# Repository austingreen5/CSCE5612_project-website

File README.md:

# CSCE5612_project-website
CSCE 5612 Project Website Link - https://austingreen5.github.io/CSCE5612_project-website/

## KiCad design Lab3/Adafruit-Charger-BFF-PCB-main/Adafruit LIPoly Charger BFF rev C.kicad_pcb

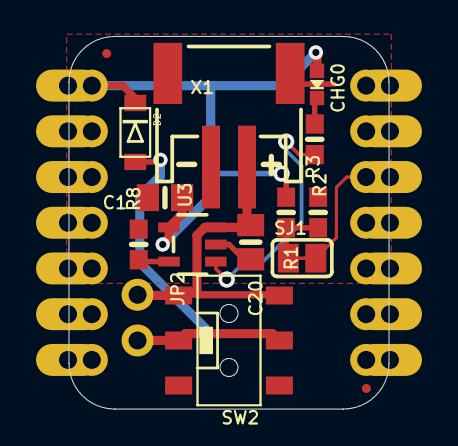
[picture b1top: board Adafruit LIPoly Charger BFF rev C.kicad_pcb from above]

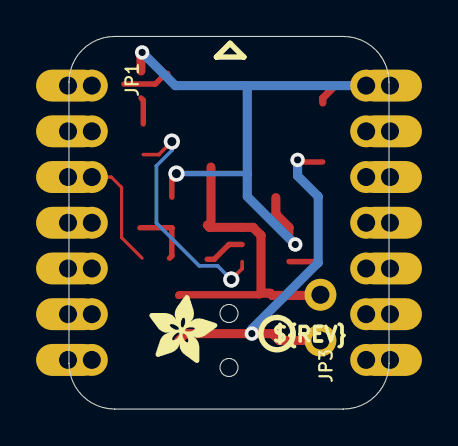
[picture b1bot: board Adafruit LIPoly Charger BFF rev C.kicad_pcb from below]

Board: 16 copper layers, 17.8 x 20.7 mm, 34 parts (7 on the bottom side), 9 nets.

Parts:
C1, C20: 10uF; 0805-NO
CHG0: ORANGE; CHIPLED_0603_NOOUTLINE
D2: MBR120; SOD-123FL
JP1, JP3: 1X07_CASTEL
JP2: 1X02_ROUND
PLABEL0: PLABEL0
PLABEL1: PLABEL1
PLABEL2: PLABEL2
PLABEL3: PLABEL3
PLABEL4: PLABEL4
PLABEL5: PLABEL5
PLABEL6: PLABEL6
PLABEL7: PLABEL7
PLABEL8: PLABEL8
PLABEL9: PLABEL9
PLABEL10: PLABEL10
PLABEL11: PLABEL11
PLABEL12: PLABEL12
PLABEL13: PLABEL13
PLABEL14: PLABEL14
R1, R3: 100K; 0603-NO
R2, R8: 5.1K; 0603-NO
SJ1: SOLDERJUMPER_CLOSEDWIRE
SW2: EG1390
U3: MCP73831T-2ACI/OT; SOT23-5
U$2: ADAFRUIT_3.5MM
U$3: PCBFEAT-REV-040
U$6, U$8: FIDUCIAL_0.5MM
X1: JSTPH; JSTPH2_BATT

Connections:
+5V: C1.1, CHG0.A, D2.C, JP3.7, JP3.7C, R1.1, U3.4
A2: JP1.3, JP1.3C, SJ1.2
GND: C1.2, C20.2, JP3.6, JP3.6C, R3.2, R8.2, U3.2, X1.1, X1.NC1, X1.NC2
unnamed: R1.2, R3.1, SJ1.1
unnamed: CHG0.C, R2.1
unnamed: R2.2, U3.1
unnamed: R8.1, U3.5
unnamed: D2.A, JP2.2, SW2.P1, SW2.P2
VBAT: C20.1, JP2.1, SW2.S1, SW2.S2, U3.3, X1.2

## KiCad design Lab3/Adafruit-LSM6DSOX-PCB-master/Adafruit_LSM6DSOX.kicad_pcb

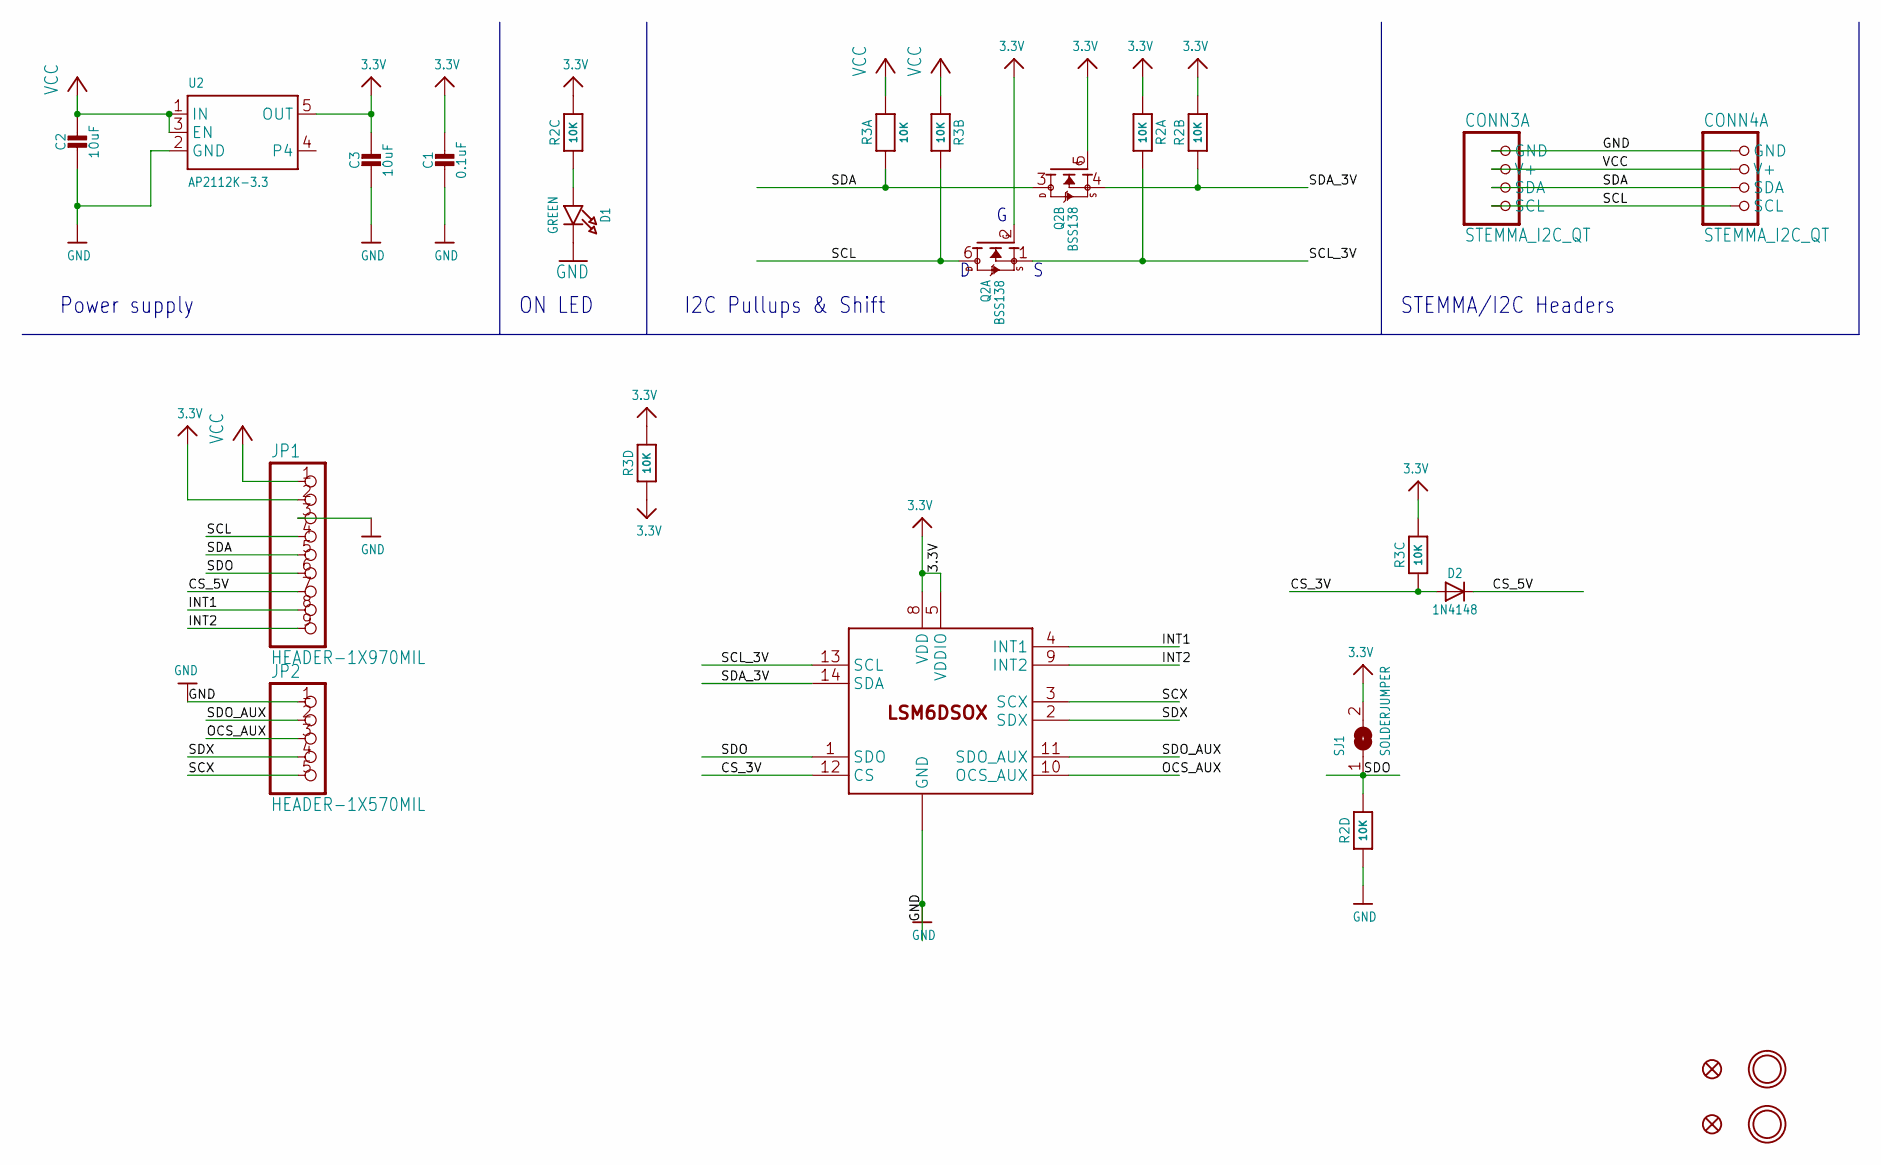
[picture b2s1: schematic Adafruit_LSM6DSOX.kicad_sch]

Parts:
C1: 0.1uF; 0603-NO
C2, C3: 10uF; 0805-NO
CONN3, CONN4: STEMMA_I2C_QT; JST_SH4
D1: GREEN; CHIPLED_0603_NOOUTLINE
D2: 1N4148; SOD-323
FID3, FID4: FIDUCIAL_1MM
JP1: HEADER-1X970MIL; 1X09_ROUND_70
JP2: HEADER-1X570MIL; 1X05_ROUND_70
Q2: BSS138; SOT363
R2, R3: 10K; RESPACK_4X0603
SJ1: SOLDERJUMPER; SOLDERJUMPER_ARROW_NOPASTE
U2: AP2112K-3.3; SOT23-5
U$1, U$17: MOUNTINGHOLE2.5; MOUNTINGHOLE_2.5_PLATED
U$2: LSM6DSOX; LGA-14L

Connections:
3.3V: C1.1, C3.1, JP1.2, Q2.2 (G), Q2.5 (G), R2.1, R2.2 (1), R2.6 (2), R3.3 (1), R3.4 (1), R3.5 (2), SJ1.2, U2.5 (OUT), U$2.5 (VDDIO), U$2.8 (VDD)
CS_3V: D2.A, R3.6 (2), U$2.12 (CS)
CS_5V: D2.C, JP1.7
GND: C1.2, C2.2, C3.2, CONN3.1 (GND), CONN4.1 (GND), D1.C, JP1.3, JP2.1, R2.4 (1), U2.2 (GND), U$2.6 (GND), U$2.7 (GND)
INT1: JP1.8, U$2.4 (INT1)
INT2: JP1.9, U$2.9 (INT2)
unnamed: D1.A, R2.3 (1)
OCS_AUX: JP2.3, U$2.10 (OCS_AUX)
SCL: CONN3.4 (SCL), CONN4.4 (SCL), JP1.4, Q2.6 (D), R3.2 (1)
SCL_3V: Q2.1 (S), R2.8 (2), U$2.13 (SCL)
SCX: JP2.5, U$2.3 (SCX)
SDA: CONN3.3 (SDA), CONN4.3 (SDA), JP1.5, Q2.3 (D), R3.1
SDA_3V: Q2.4 (S), R2.7 (2), U$2.14 (SDA)
SDO: JP1.6, R2.5 (2), SJ1.1, U$2.1 (SDO)
SDO_AUX: JP2.2, U$2.11 (SDO_AUX)
SDX: JP2.4, U$2.2 (SDX)
VCC: C2.1, CONN3.2 (V+), CONN4.2 (V+), JP1.1, R3.7 (2), R3.8 (2), U2.1 (IN), U2.3 (EN)

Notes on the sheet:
ON LED
I2C Pullups & Shift
STEMMA/I2C Headers
Power supply

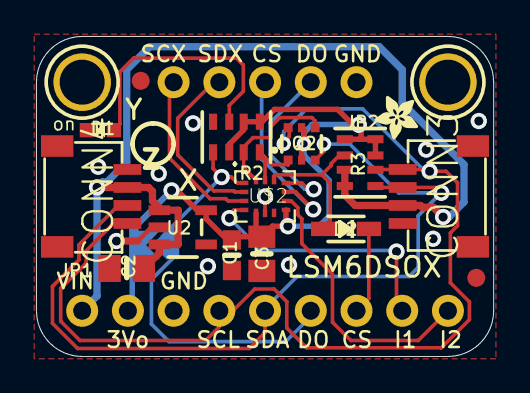
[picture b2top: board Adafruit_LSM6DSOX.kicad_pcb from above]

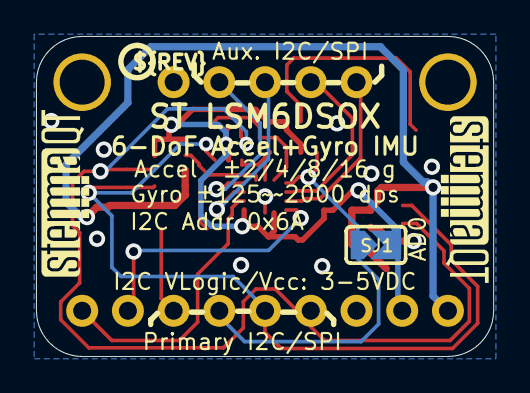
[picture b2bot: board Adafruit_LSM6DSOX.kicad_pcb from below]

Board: 2 copper layers, 25.4 x 17.8 mm, 23 parts (4 on the bottom side), 17 nets.

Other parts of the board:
U$9: ADAFRUIT_2.5MM
U$25: PCBFEAT-REV-040
U$30, U$31: STEMMAQT

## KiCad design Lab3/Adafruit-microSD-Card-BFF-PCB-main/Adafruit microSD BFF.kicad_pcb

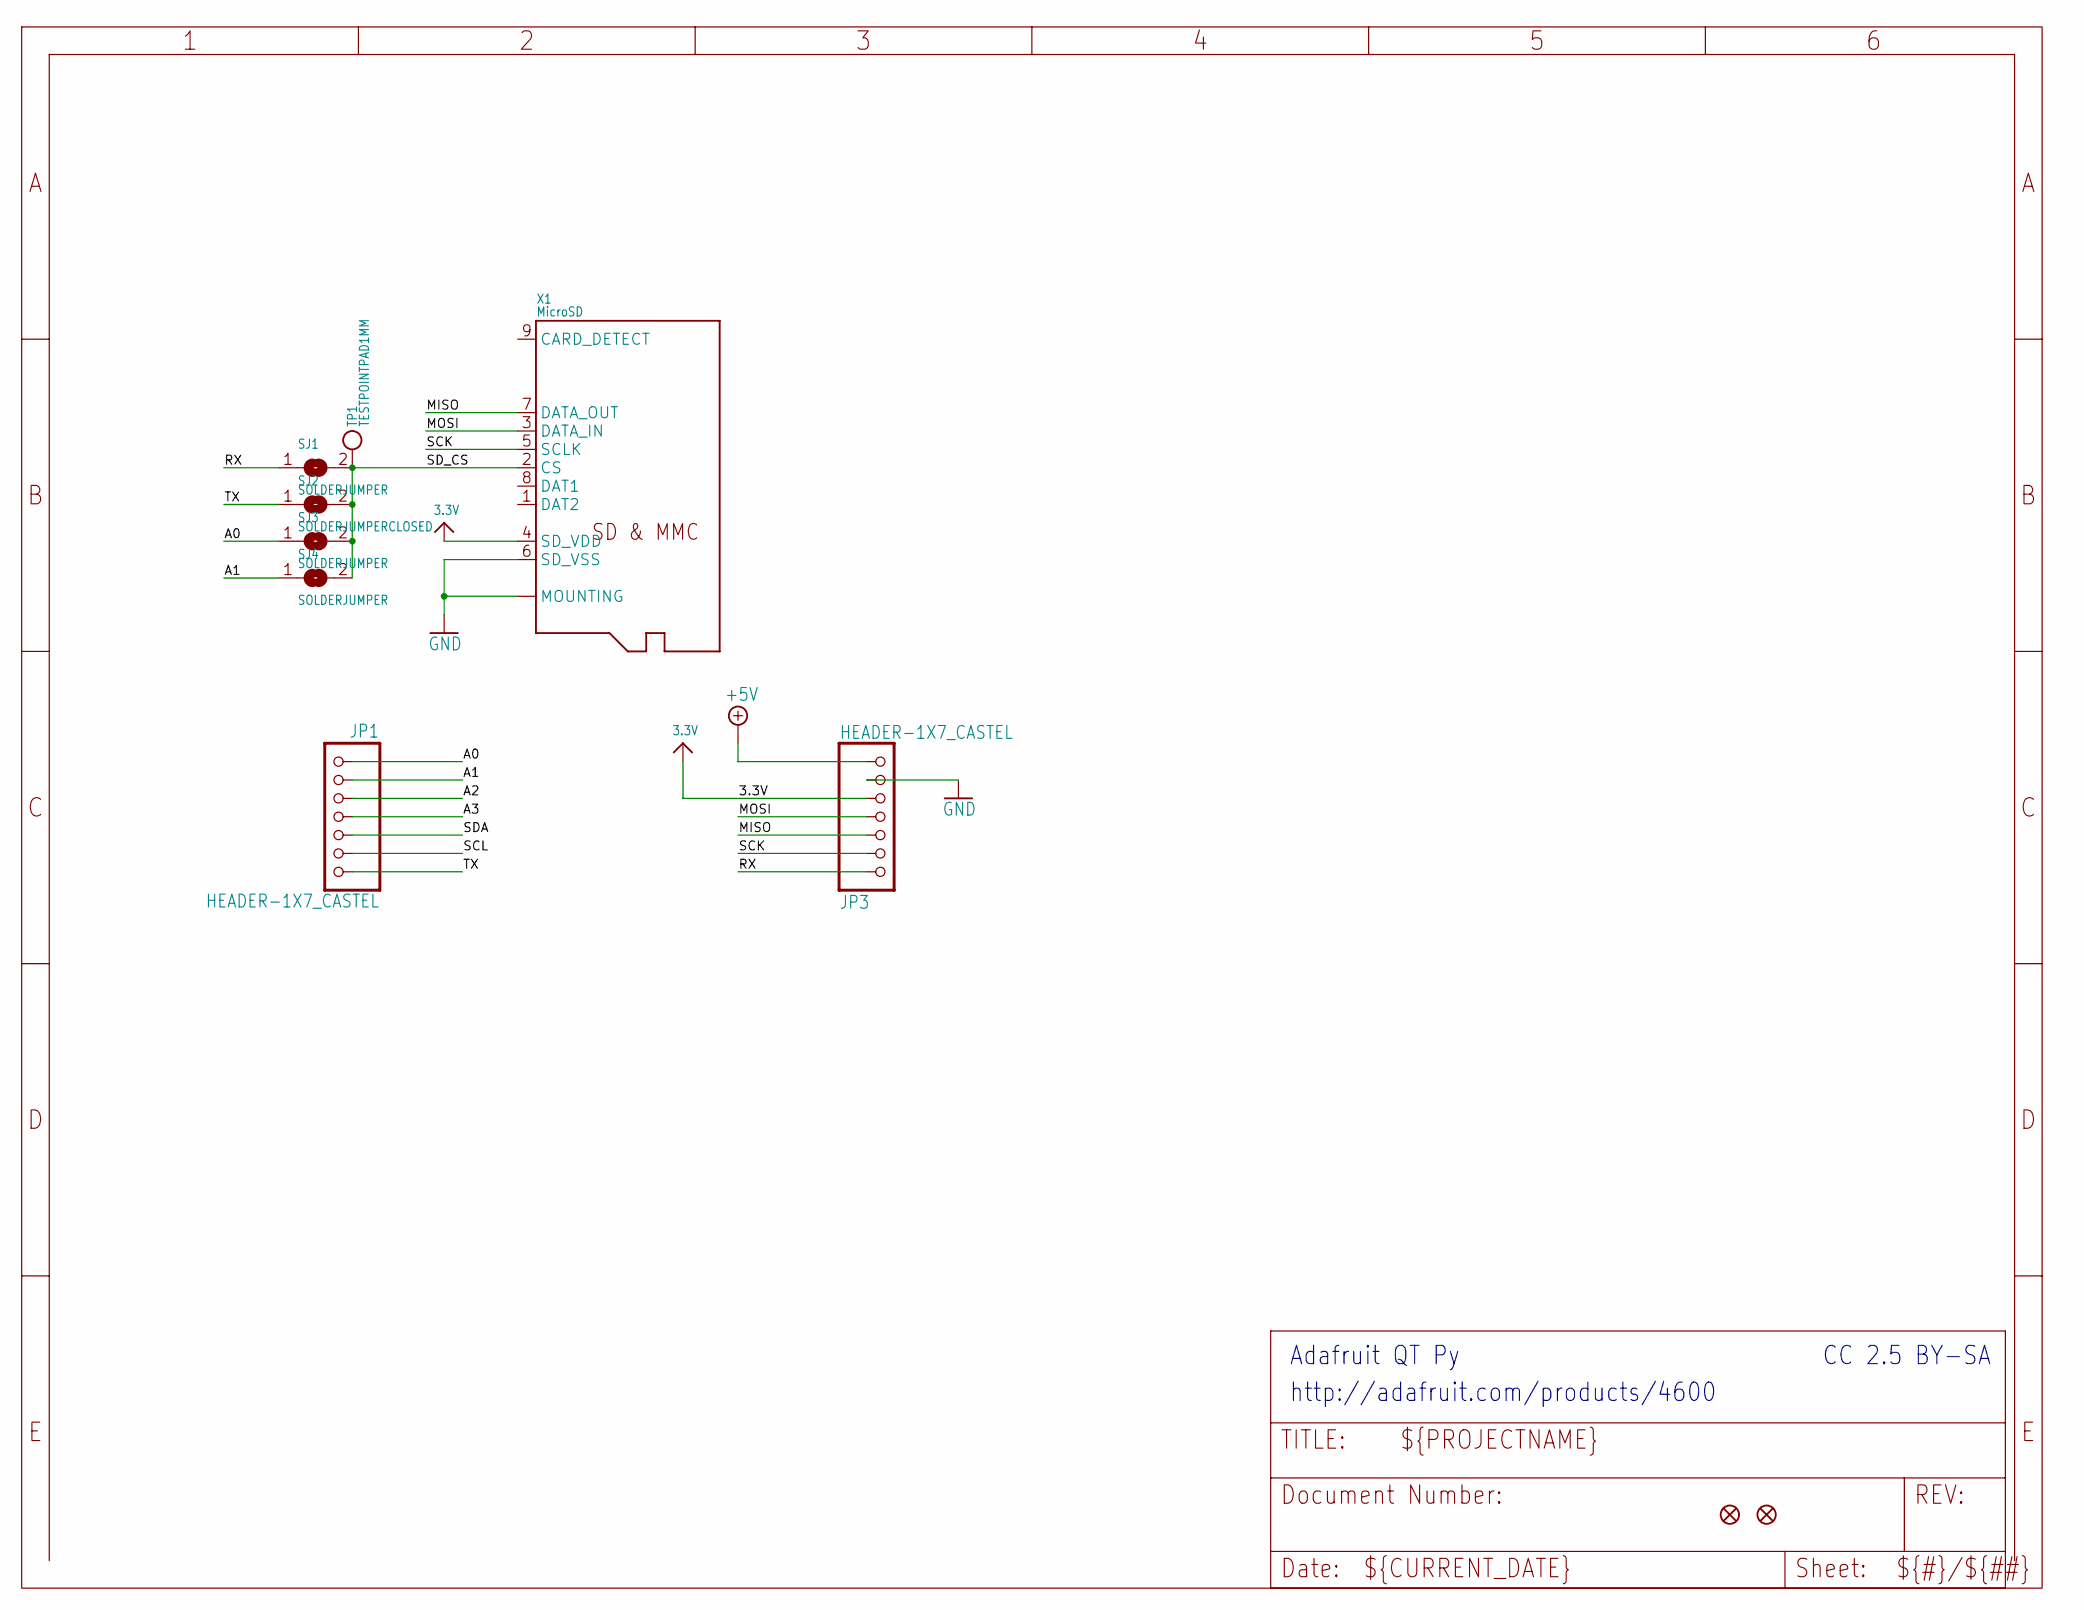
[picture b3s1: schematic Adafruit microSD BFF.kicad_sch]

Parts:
JP1, JP3: HEADER-1X7_CASTEL; 1X07_CASTEL
SJ1, SJ3, SJ4: SOLDERJUMPER; SOLDERJUMPER_ARROW_NOPASTE
SJ2: SOLDERJUMPERCLOSED; SOLDERJUMPER_CLOSEDWIRE
TP1: TESTPOINTPAD1MM; TESTPOINT_PAD_1MM
U$6, U$8: FIDUCIAL_1MM
X1: MicroSD; MOLEX_104031-0811

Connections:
3.3V: JP3.5, JP3.5C (5), X1.4 (SD_VDD)
+5V: JP3.7, JP3.7C (7)
A0: JP1.1, JP1.1C (1), SJ3.1
A1: JP1.2, JP1.2C (2), SJ4.1
A2: JP1.3, JP1.3C (3)
A3: JP1.4, JP1.4C (4)
GND: JP3.6, JP3.6C (6), X1.6 (SD_VSS), X1.10 (MOUNTING), X1.G1 (MOUNTING), X1.G2 (MOUNTING), X1.G3 (MOUNTING), X1.G4 (MOUNTING)
MISO: JP3.3, JP3.3C (3), X1.7 (DATA_OUT)
MOSI: JP3.4, JP3.4C (4), X1.3 (DATA_IN)
RX: JP3.1, JP3.1C (1), SJ1.1
SCK: JP3.2, JP3.2C (2), X1.5 (SCLK)
SCL: JP1.6, JP1.6C (6)
SDA: JP1.5, JP1.5C (5)
SD_CS: SJ1.2, SJ2.2, SJ3.2, SJ4.2, TP1.P$1, X1.2 (CS)
TX: JP1.7, JP1.7C (7), SJ2.1

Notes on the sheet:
http://adafruit.com/products/4600
Adafruit QT Py
CC 2.5 BY-SA

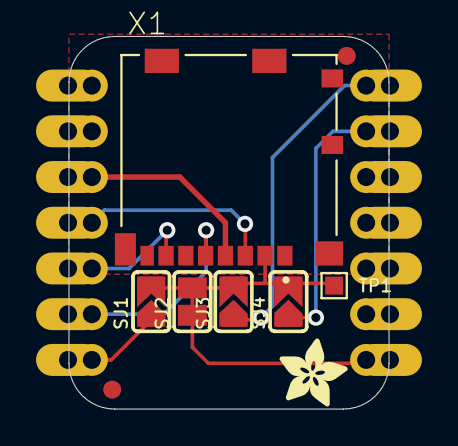
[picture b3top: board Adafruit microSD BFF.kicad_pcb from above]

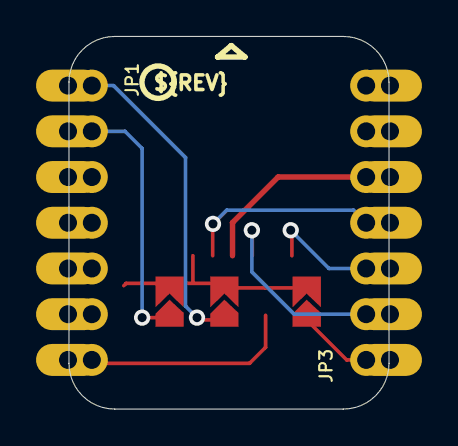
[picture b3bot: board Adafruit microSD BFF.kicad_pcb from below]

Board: 16 copper layers, 17.8 x 20.7 mm, 20 parts (5 on the bottom side), 15 nets.

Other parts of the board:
PLABEL0: PLABEL0
PLABEL1: PLABEL1
PLABEL2: PLABEL2
PLABEL3: PLABEL3
PLABEL4: PLABEL4
PLABEL5: PLABEL5
PLABEL6: PLABEL6
PLABEL7: PLABEL7
U$2: ADAFRUIT_3.5MM
U$3: PCBFEAT-REV-040

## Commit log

2026-01-14 Upload Screenshots of Lab 1
2026-01-14 Add Lab 1 Images to index file
2026-01-14 Name images
2026-01-14 reorganize files
2026-01-22 add Lab1 & 2 Code
2026-01-22 input second week screenshots
2026-01-22 add website link to readme
2026-02-04 init Lab3
2026-02-04 ActivityTracker Schematic
2026-02-04 update index
2026-02-06 Lab3 support files
2026-02-06 part2
2026-02-06 add Lab2 updates to index
2026-02-06 add SD card data
2026-02-11 step code
2026-02-11 change broadcast name
2026-02-18 add lab
2026-02-18 add ActivityTracker project
2026-02-18 Gesture Recognition Website
2026-02-18 add python collection file
2026-02-18 working project - got punch data
